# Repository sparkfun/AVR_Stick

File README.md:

SparkFun AVR Stick
========================================

[*SparkFun AVR Stick (DEV-09147)*](https://www.sparkfun.com/products/9147)

 The SparkFun AVR Stick is a simple data logging device that instantiates itself as an HID keyboard and reports the voltages, along with a ‘timestamp,’ from two pins on an ATtiny85.
 
Repository Contents
-------------------

* **/Firmware** - Example code 
* **/Hardware** - Eagle design files (.brd, .sch)
* **/Production** - Production panel files (.brd)

Documentation
--------------
* **[SparkFun Fritzing repo](https://github.com/sparkfun/Fritzing_Parts)** - Fritzing diagrams for SparkFun products.
* **[SparkFun 3D Model repo](https://github.com/sparkfun/3D_Models)** - 3D models of SparkFun products. 

License Information
-------------------
This product is _**open source**_! 

The **hardware** is released under [Creative Commons ShareAlike 4.0 International](https://creativecommons.org/licenses/by-sa/4.0/).

Please use, reuse, and modify these files as you see fit. Please maintain attribution to SparkFun Electronics and release anything derivative under the same license.

Distributed as-is; no warranty is given.

- Your friends at SparkFun.

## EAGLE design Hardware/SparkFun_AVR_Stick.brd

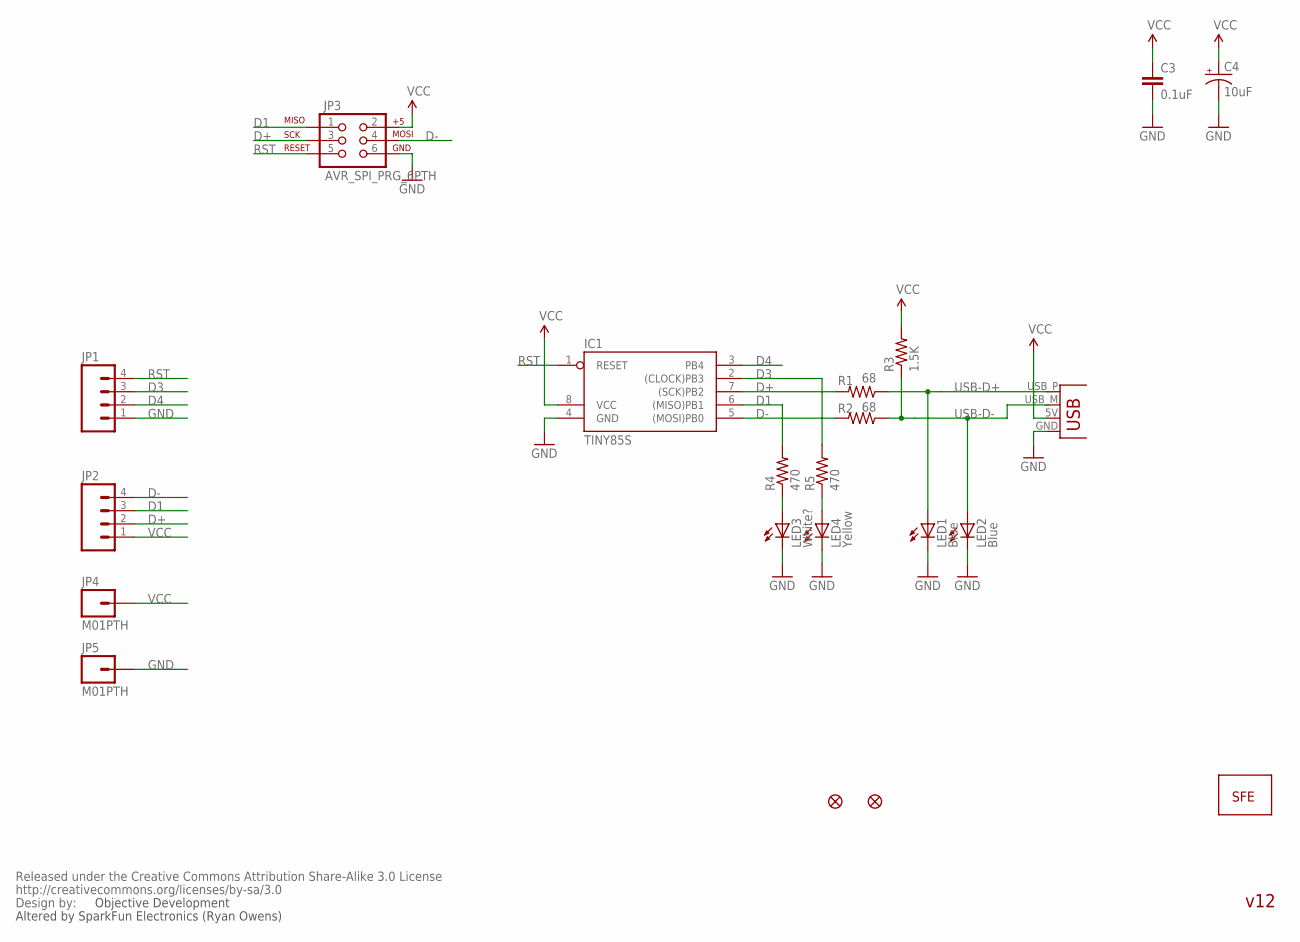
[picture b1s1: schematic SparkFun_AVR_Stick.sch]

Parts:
C3: 0.1uF; 0402-CAP
C4: 10uF; EIA3216
IC1: TINY85S; SOIC8
JP1, JP2: M04PTH; 1X04
JP3: AVR_SPI_PRG_6PTH; 2X3
JP4, JP5: M01PTH; 1X01
LED1, LED2: Blue; LED-0603
LED3: White?; LED-0603
LED4: Yellow; LED-0603
R1, R2: 68; 0402-RES
R3: 1.5K; 0402-RES
R4, R5: 470; 0402-RES
U$1: LOGO-SFESK; SFE-LOGO-FLAME
U$2, U$3: FIDUCIAL1X2; FIDUCIAL-1X2
U$4: CREATIVE_COMMONS
X1: USBPCB; USB-A-PCB

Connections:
D1: IC1.6 ((MISO)PB1), JP2.3, JP3.1, R4.2
D3: IC1.2 ((CLOCK)PB3), JP1.3, R5.2
D4: IC1.3 (PB4), JP1.2
D+: IC1.7 ((SCK)PB2), JP2.2, JP3.3, R1.2
D-: IC1.5 ((MOSI)PB0), JP2.4, JP3.4, R2.2
GND: C3.2, C4.C (-), IC1.4 (GND), JP1.1, JP3.6, JP5.1, LED1.C, LED2.C, LED3.C, LED4.C, X1.GND
unnamed: LED3.A, R4.1
unnamed: LED4.A, R5.1
RST: IC1.1 (RESET), JP1.4, JP3.5
USB-D+: LED1.A, R1.1, X1.USB_P (D+)
USB-D-: LED2.A, R2.1, R3.1, X1.USB_M (D-)
VCC: C3.1, C4.A (+), IC1.8 (VCC), JP2.1, JP3.2, JP4.1, R3.2, X1.5V (VBUS)

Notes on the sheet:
Objective Development
Altered by SparkFun Electronics (Ryan Owens)
v12

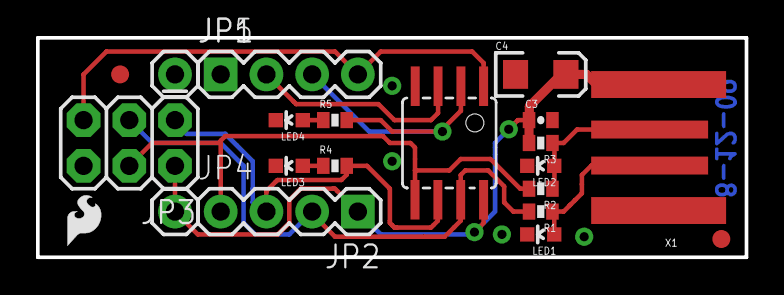
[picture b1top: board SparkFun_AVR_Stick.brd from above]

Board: 2 copper layers, 39.4 x 12.2 mm, 22 parts (0 on the bottom side), 12 nets.

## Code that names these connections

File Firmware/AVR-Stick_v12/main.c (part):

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
/*
Pin assignment:
PB3 = analog input (ADC3)
PB4 = analog input (ADC2) - Can alternately be used as an LED output.
PB1 = LED output

PB0, PB2 = USB data lines
*/

#define WHITE_LED 3
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/* ------------------------------------------------------------------------- */
static void adcInit(void)
{
    ADMUX = UTIL_BIN8(1001, 0010);	 /* vref = 2.56V, measure ADC2 (PB4) */
	ADCSRA = UTIL_BIN8(1000, 0111); /* enable ADC, not free running, interrupt disable, rate = 1/128 */
}

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
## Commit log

2015-05-07 adding hardware files

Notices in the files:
Firmware/AVR-Stick_v12/main.c:
Copyright: (c) 2006 by OBJECTIVE DEVELOPMENT Software GmbH
License: Proprietary, free under certain conditions. See Documentation.
parts and their libraries:
SparkFun: Released under the Creative Commons Attribution Share-Alike 3.0 License
SparkFun: http://creativecommons.org/licenses/by-sa/3.0
